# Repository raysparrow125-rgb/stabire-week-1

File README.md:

The starbie PCB project Week 1 has been complete for me! In this ReadMe Ill just be saying what Ive done for Week 1!

So basically a Starbie or a StarBoy is like a digital pet or trinket you can collect. This star can respond to many gestures and can see and feel the area around it! A pretty cool thing right?

Anyways, Ive followed a guide about it and learned how to use Kicad and Arduino IDE. Its pretty fun to do and learn about how it works and the components inside.

(Inside the PCB editor)

(inside the Schematic editor)

Excited to continue my weeks in Hack club and cant wait to see what I will do next!

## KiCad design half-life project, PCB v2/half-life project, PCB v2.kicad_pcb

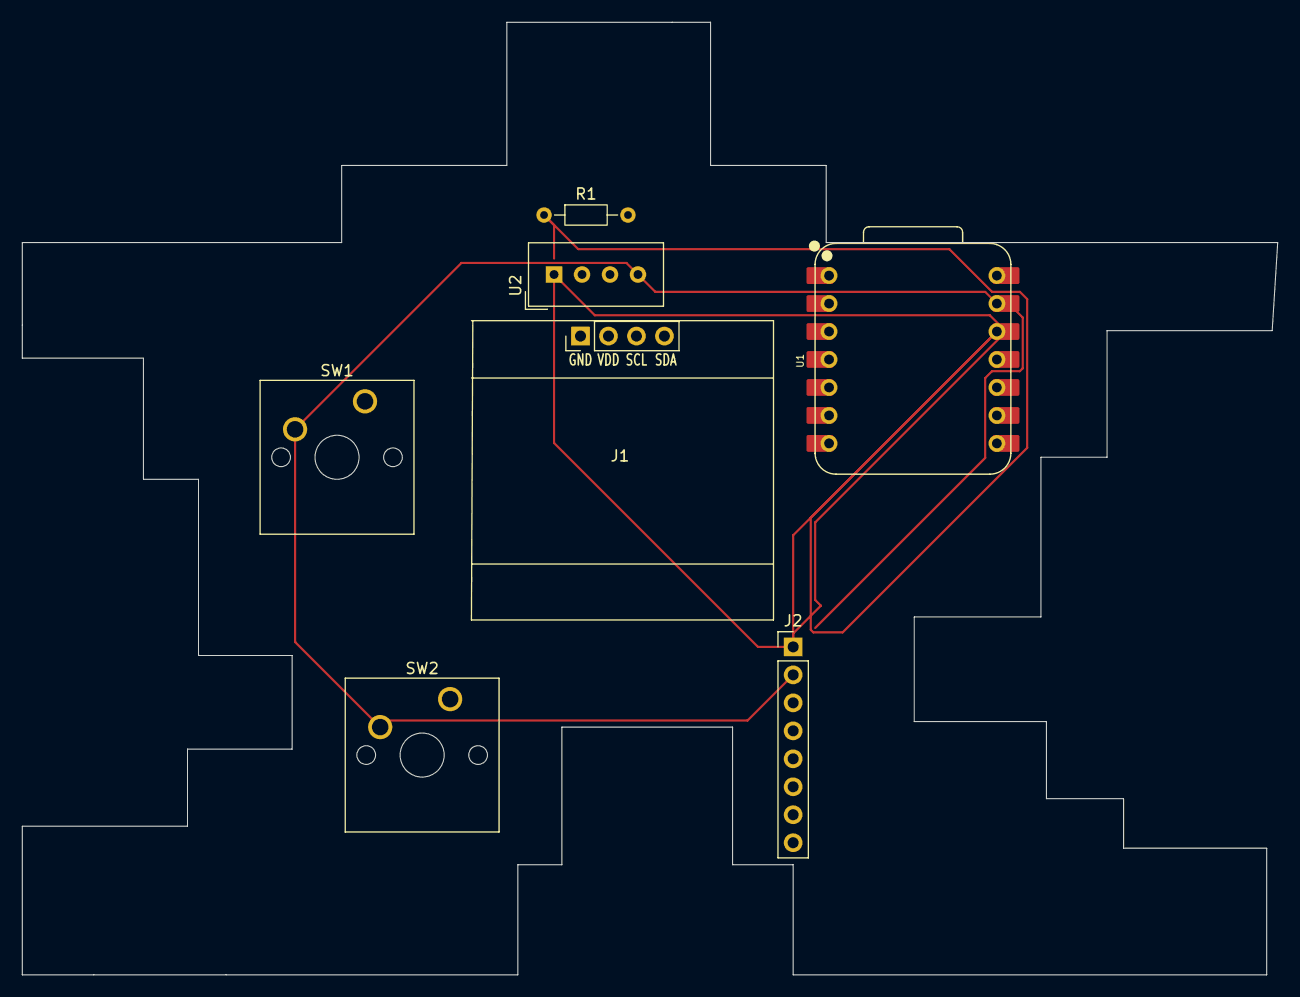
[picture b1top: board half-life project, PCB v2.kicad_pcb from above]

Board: 2 copper layers, 114.0 x 86.5 mm, 7 parts (0 on the bottom side), 2 nets.

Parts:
J1: Conn_01x04_Pin; Display_128x64_096_I2C
J2: Conn_01x08_Pin; PinHeader_1x08_P2.54mm_Vertical
R1: 10k; R_Axial_DIN0204_L3.6mm_D1.6mm_P7.62mm_Horizontal
SW1, SW2: SW_Push; SW_Cherry_MX_1.00u_PCB
U1: XIAO-ESP32-C3-SMD; XIAO-ESP32-C6-DIP
U2: DHT11; Aosong_DHT11_5.5x12.0_P2.54mm

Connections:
+3.3V: J2.1, R1.1, U1.12 (3V3_OUT), U2.1 (VDD)
GND: J2.2, SW1.2 (2_2), SW2.2 (2_2), U1.13 (GND), U2.4 (GND)
